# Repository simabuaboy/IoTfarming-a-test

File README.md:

# IoT Sensor Data Post

This project is designed to read data from various sensors, format the data into a JSON payload, and post the payload to a specific URL every minute. The project is built for the ESP32 microcontroller using the ESP-IDF libraries and FreeRTOS.

## Sensors

The project reads data from the following sensors:

- Soil Moisture Sensor: Measures the moisture level of the soil.

- Air Temperature Sensor: Measures the temperature of the air.

- Anemometer (Wind Speed Sensor): Measures the speed of the wind.

- Sunlight Sensor: Measures the intensity of sunlight.

## Data Posting

The sensor data is posted to the following URL: `https://cisea.bukitasam.co.id/api-iot/api/v1/iot/iot-test/post`

The data is posted in the following JSON format:

```json
{

   "sensor_code":"FF-001",

   "location":"Blok Timur A",

   "timestamp":"2023-09-11 10:30:00",

   "data":{

      "soil_moisture":45.6,

      "air_temperature":28.2,

      "wind_speed":5.4,

      "sunlight_intensity":750

   }
}

```

## FreeRTOS

The project uses FreeRTOS to create a task that reads the sensor data, formats the JSON payload, and posts the payload every minute. The task is pinned to core 1 of the ESP32.

## Building and Running

To build the project, navigate to the project directory and run the following command:

`idf.py build`

To flash the project onto the ESP32, connect the ESP32 to your computer and run the following command:

`idf.py -p PORT flash`

Replace `PORT` with the port that the ESP32 is connected to.

To view the output of the ESP32, run the following command:

`idf.py -p PORT monitor`

Replace `PORT` with the port that the ESP32 is connected to.

## Note

- The Project use hardware dummies, ie using some sort of mocked class to simulate the hardware
- all the sensor class use the esp-idf paradigm components to seperate HAL code or userinterface codes
- the **code can be build** 
- it used esp-idf release/v4.4
- 

## esp-idf instalation
- head to this url for esp-idf instalation : https://docs.espressif.com/projects/esp-idf/en/stable/esp32/get-started/index.html
-

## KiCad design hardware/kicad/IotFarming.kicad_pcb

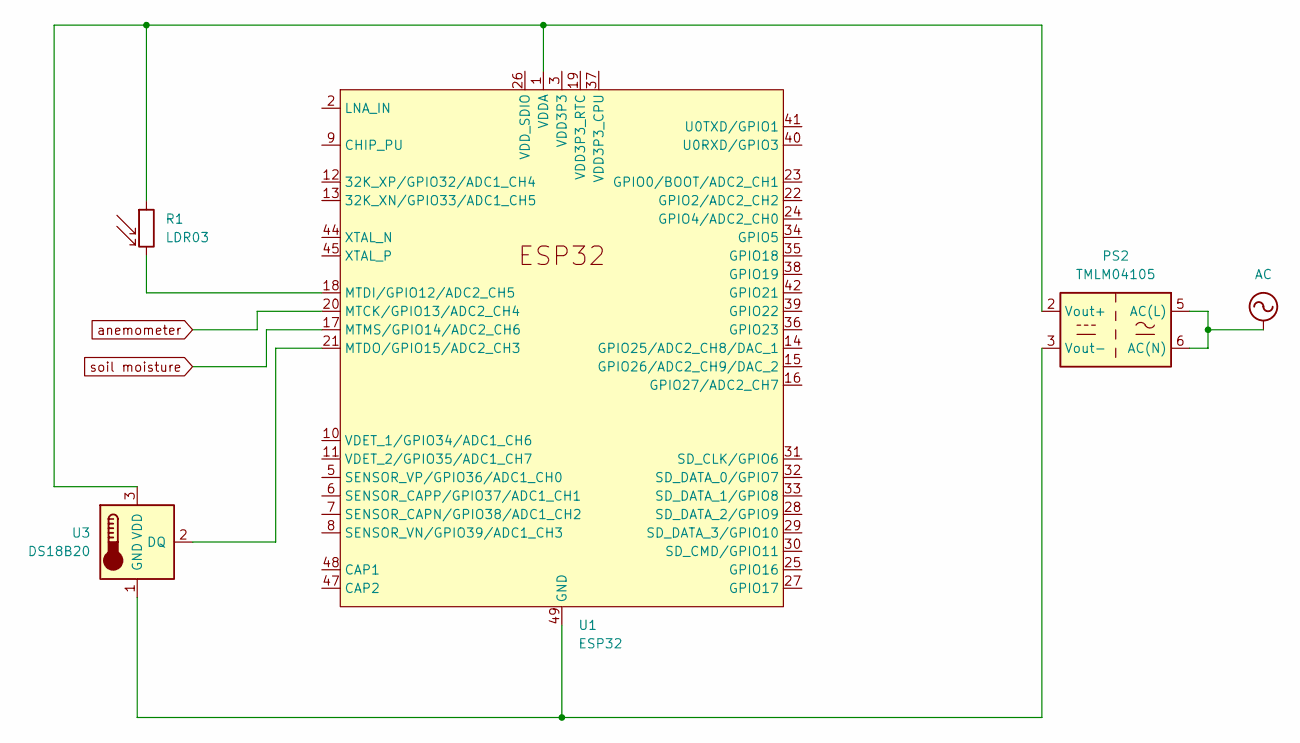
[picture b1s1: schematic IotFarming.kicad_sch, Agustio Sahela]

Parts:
PS2: TMLM04105; Converter_ACDC_TRACO_TMLM-04_THT
R1: LDR03; R_LDR_10x8.5mm_P7.6mm_Vertical
U1: ESP32; QFN-48-1EP_6x6mm_P0.4mm_EP4.3x4.3mm
U3: DS18B20; TO-92_Inline

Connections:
AC: PS2.5 (AC(L)), PS2.6 (AC(N))
unnamed: PS2.2 (Vout+), R1.1, U1.1 (VDDA), U1.43 (VDDA), U1.46 (VDDA), U3.3 (VDD)
unnamed: PS2.3 (Vout-), U1.49 (GND), U3.1 (GND)
unnamed: R1.2, U1.18 (MTDI/GPIO12/ADC2_CH5)
unnamed: U1.21 (MTDO/GPIO15/ADC2_CH3), U3.2 (DQ)
unnamed: U1.3 (VDD3P3), U1.4 (VDD3P3)
anemometer: U1.20 (MTCK/GPIO13/ADC2_CH4)
soil moisture: U1.17 (MTMS/GPIO14/ADC2_CH6)

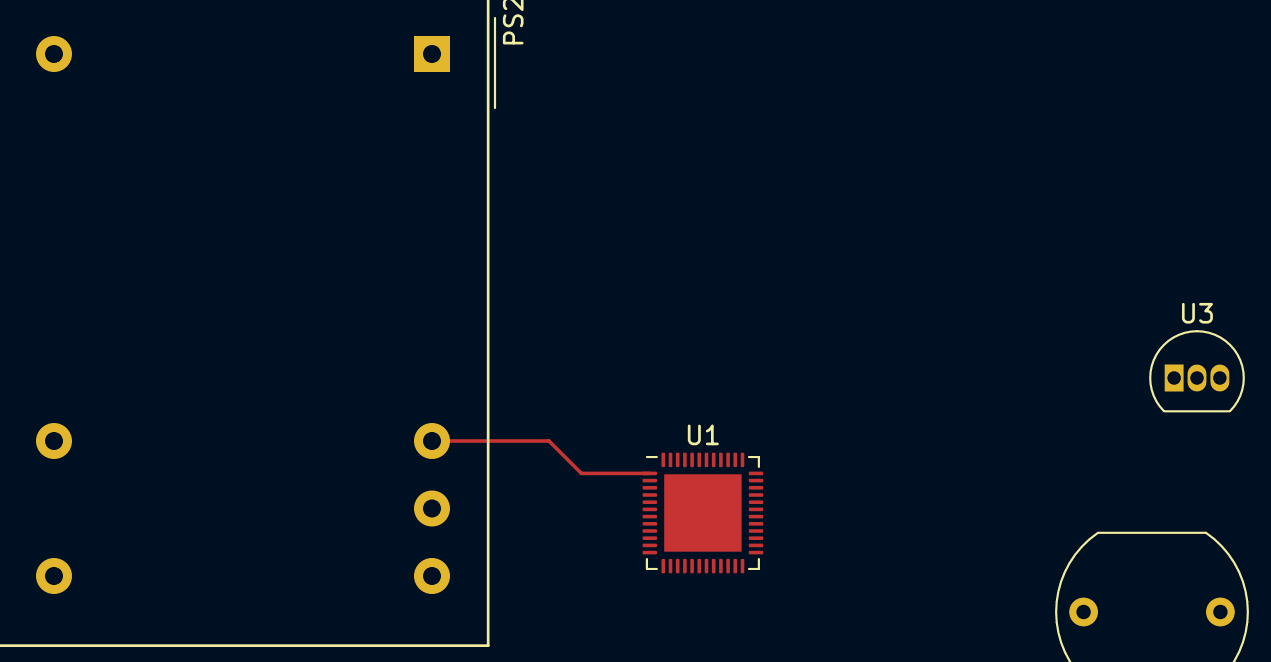
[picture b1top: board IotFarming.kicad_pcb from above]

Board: 2 copper layers, 4 parts (0 on the bottom side), 6 nets.

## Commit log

2024-04-24 docs(update): gitignore, readme
2024-04-24 feature(sensors): adding sensors
2024-04-24 feature(interfaces): adding http and ntp client
2024-04-24 feat(main): adding all up to the main
2024-04-24 docs(hardware): hardware design
2024-04-24 doc(readme): update readme
2024-04-24 doc(readme): updaet
